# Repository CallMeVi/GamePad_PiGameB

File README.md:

# GamePad_PiGameB
Gamepad for raspberry game boy

For any info contact me in PM or visit my personal page: http://www.vincenzogermano.com/

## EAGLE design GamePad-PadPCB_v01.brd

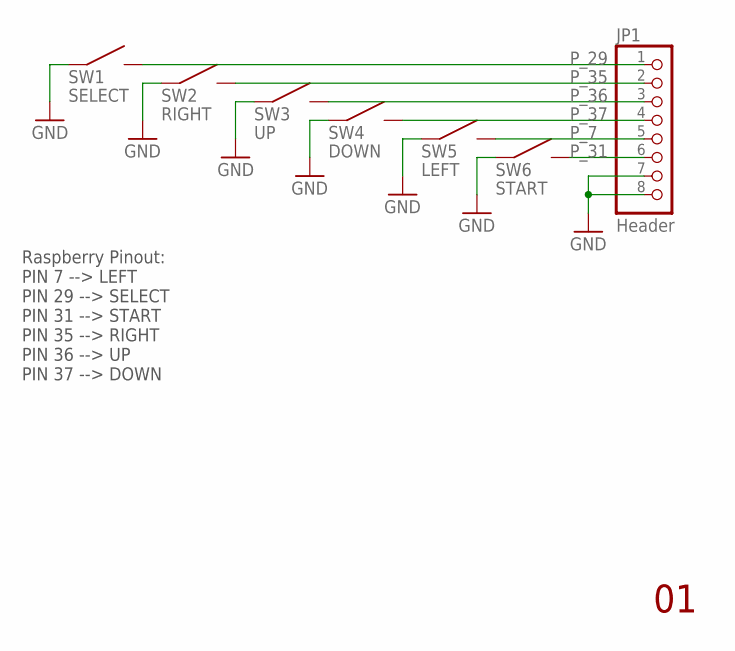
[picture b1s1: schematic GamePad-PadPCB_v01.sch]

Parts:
JP1: Header; 1X08
SW1: SELECT; EVPA
SW2: RIGHT; EVPA
SW3: UP; EVPA
SW4: DOWN; EVPA
SW5: LEFT; EVPA
SW6: START; EVPA

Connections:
GND: JP1.7, JP1.8, SW1.1, SW2.1, SW3.1, SW4.1, SW5.1, SW6.1
P_7: JP1.5, SW5.2
P_29: JP1.1, SW1.2
P_31: JP1.6, SW6.2
P_35: JP1.2, SW2.2
P_36: JP1.3, SW3.2
P_37: JP1.4, SW4.2

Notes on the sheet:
Raspberry Pinout: PIN 7 --> LEFT PIN 29 --> SELECT PIN 31 --> START PIN 35 --> RIGHT PIN 36 --> UP PIN 37 --> DOWN

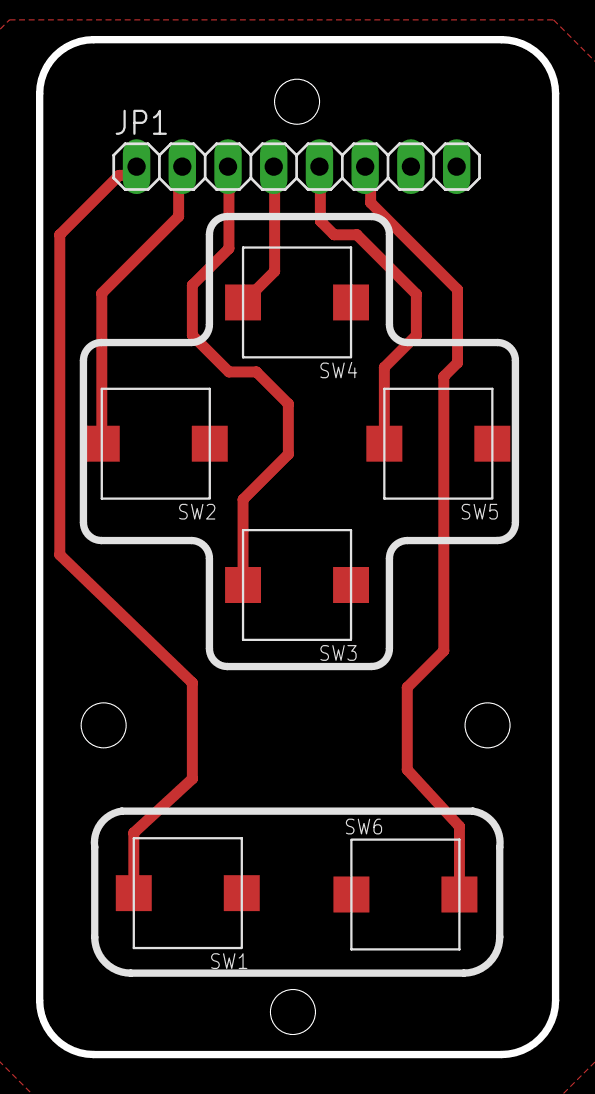
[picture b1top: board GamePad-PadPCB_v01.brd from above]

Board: 2 copper layers, 28.7 x 56.4 mm, 7 parts (0 on the bottom side), 7 nets.

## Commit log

2018-05-15 First Release of PadPCB
